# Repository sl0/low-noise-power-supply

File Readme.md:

# Low noise power supply

Noise on the power supply is disturbing, especially when you have some RF
components. Recently I got a hint to a work of Bernhard DG4RBF about his
paper on
[Rauschmessungen am LM723][].

Thanks to DF7KB and DC6CM for their helpful details and verifying the schema and the PCB,
which finally led to this KiCAD version using a LM723 and a PNP
transistor BD244C.

The files in the kicad directoy are licensed under the terms of the definition
for Open Source Hardware Association.

It is a simple schema as screenshot from my KiCAD session:

You have to decide which Voltage you need:

 - Output lower than 7.15 V:

    use R1 for adjusting, R7 may be replaced by a wire on pins 3+2, R8 is not needed at all.

 - Output greater than 7.15 V:

    use R7 for adjusting, R1 is not needed

C4 is doubled now with C9, ultra low noise should use 1000nF in sum.

If you don't need the ultra low noise feature, just bridge R4 and
reduce C4, C9 to 100nF.

R9, C7 and U2 provide a reference voltage, f.e. for ardiuno Aref to
make exact measurements possible. If you you don't need this, just
omit them on the pcb.

Have fun!

[Rauschmessungen am LM723]: https://dg4rbf.lima-city.de/Rauschmessungen%20am%20LM723.pdf

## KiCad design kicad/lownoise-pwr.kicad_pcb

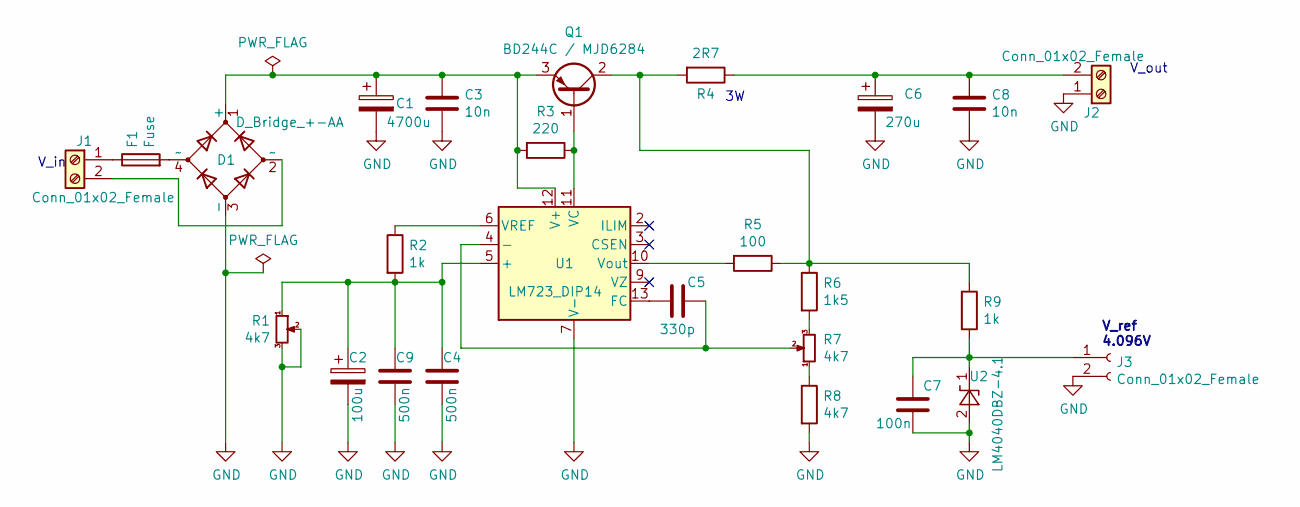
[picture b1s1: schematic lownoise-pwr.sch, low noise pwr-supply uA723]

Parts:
C1: 4700u; C_Radial_D18.0mm_H35.5mm_P7.50mm
C2: 100u; C_Radial_D8.0mm_H7.0mm_P3.50mm
C3, C8: 10n; C_1206_3216Metric_Pad1.42x1.75mm_HandSolder
C4, C9: 500n; C_Disc_D5.0mm_W2.5mm_P2.50mm
C5: 330p; C_Radial_D5.0mm_H7.0mm_P2.00mm
C6: 270u; C_Radial_D8.0mm_H11.5mm_P3.50mm
C7: 100n; C_1210_3225Metric_Pad1.42x2.65mm_HandSolder
D1: D_Bridge_+-AA; Diode_Bridge_15.2x15.2x6.3mm_P10.9mm
F1: Fuse; Fuseholder_Cylinder-5x20mm_Schurter_0031_8201_Horizontal_Op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
J1, J2: Conn_01x02_Female; TerminalBlock_Phoenix_MKDS-3-2-5.08_1x02_P5.08mm_Horizontal
J3: Conn_01x02_Female; PinHeader_1x02_P2.54mm_Vertical
Q1: BD244C / MJD6284; TO-247-3_Vertical
R1, R7: 4k7; Potentiometer_Bourns_3296W_Vertical
R2: 1k; R_Axial_DIN0207_L6.3mm_D2.5mm_P7.62mm_Horizontal
R3: 220; R_Axial_DIN0207_L6.3mm_D2.5mm_P7.62mm_Horizontal
R4: 2R7; R_Axial_DIN0516_L15.5mm_D5.0mm_P5.08mm_Vertical
R5: 100; R_Axial_DIN0207_L6.3mm_D2.5mm_P7.62mm_Horizontal
R6: 1k5; R_Axial_DIN0207_L6.3mm_D2.5mm_P7.62mm_Horizontal
R8: 4k7; R_Axial_DIN0207_L6.3mm_D2.5mm_P7.62mm_Horizontal
R9: 1k; R_1206_3216Metric_Pad1.42x1.75mm_HandSolder
U1: LM723_DIP14; DIP-14_W7.62mm
U2: LM4040DBZ-4.1; SOT-23

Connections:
GND: C1.2, C2.2, C3.2, C4.2, C6.2, C7.2, C8.2, C9.2, D1.3 (-), J2.1, J3.2, R1.2, R1.3, R8.2, U1.7 (V-), U2.2 (A)
unnamed: C1.1, C3.1, D1.1 (+), Q1.3 (E), R3.2, U1.12 (V+)
unnamed: C2.1, C4.1, C9.1, R1.1, R2.2, U1.5 (+)
unnamed: C5.1, R7.2, U1.4 (-)
unnamed: C5.2, U1.13 (FC)
unnamed: C6.1, C8.1, J2.2, R4.1
unnamed: C7.1, J3.1, R9.2, U2.1 (K)
unnamed: D1.2 (~~), J1.2
unnamed: D1.4 (~~), F1.2
unnamed: F1.1, J1.1
unnamed: Q1.1 (B), R3.1, U1.11 (VC)
unnamed: Q1.2 (C), R4.2, R5.1, R6.1, R9.1
unnamed: R2.1, U1.6 (VREF)
unnamed: R5.2, U1.10 (Vout)
unnamed: R6.2, R7.3
unnamed: R7.1, R8.1

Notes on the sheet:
V_ref 4.096V
V_out
V_in

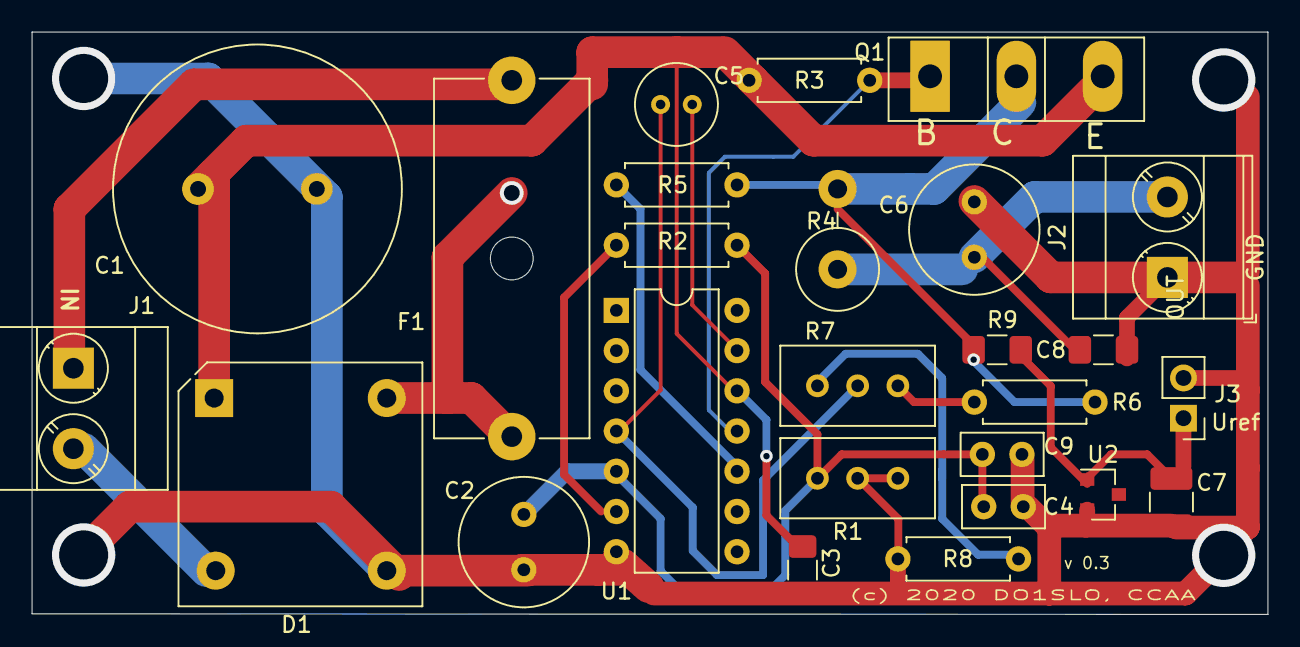
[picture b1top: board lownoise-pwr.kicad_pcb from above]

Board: 2 copper layers, 78.0 x 36.8 mm, 26 parts (0 on the bottom side), 16 nets.

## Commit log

2020-03-11 Initial commit
    Adds .gitignore to avoid r.pdf as product in the repo
2020-03-11 Adds first draft of Readme.md
    A Makefile to produce a (better) readable pdf from the Readme.md is included
    A first screenshot of the schema is added as well
2020-03-11 Ignores kicad *bak
2020-03-11 Adds KiCAD Files
2020-03-11 Missing Kicad files no longer mentioned in Readme
2020-03-13 Adds link to the 'Rauschmessungen' paper
2020-03-27 Enlarge power pins in and out
2020-03-27 Readme enriched about missing what and where
2020-03-29 Exports gerber files and zip for upload
2020-07-21 Starts long way to screw-plugs
2020-07-22 Adds output screw-plugs, big transistor
    R4 now vertical to gain space for screw-plugs
    Input srew-plug not completely on PCB, soldered wires preferred
    Adds 2nd via to solder polymer-fuse instead of glas fuseholder
2020-07-23 Adds gerber production files
    Modifies kicad_pcb file as well due to gerber export settings
    Gerber settings found there:
    https://support.jlcpcb.com/article/102-kicad-515---generating-gerber-and-drill-files
2020-10-25 Improves Readme and its schema picture
2020-10-25 Adds another C to ensure bigger capacity is possible
    Reason: components local availability
2020-10-25 Ensure distance to pcb-edge, places C4, C9
    New component requires redesign

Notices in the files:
kicad/lownoise-pwr.kicad_pcb:
(c) 2020 DO1SLO, CCAA
